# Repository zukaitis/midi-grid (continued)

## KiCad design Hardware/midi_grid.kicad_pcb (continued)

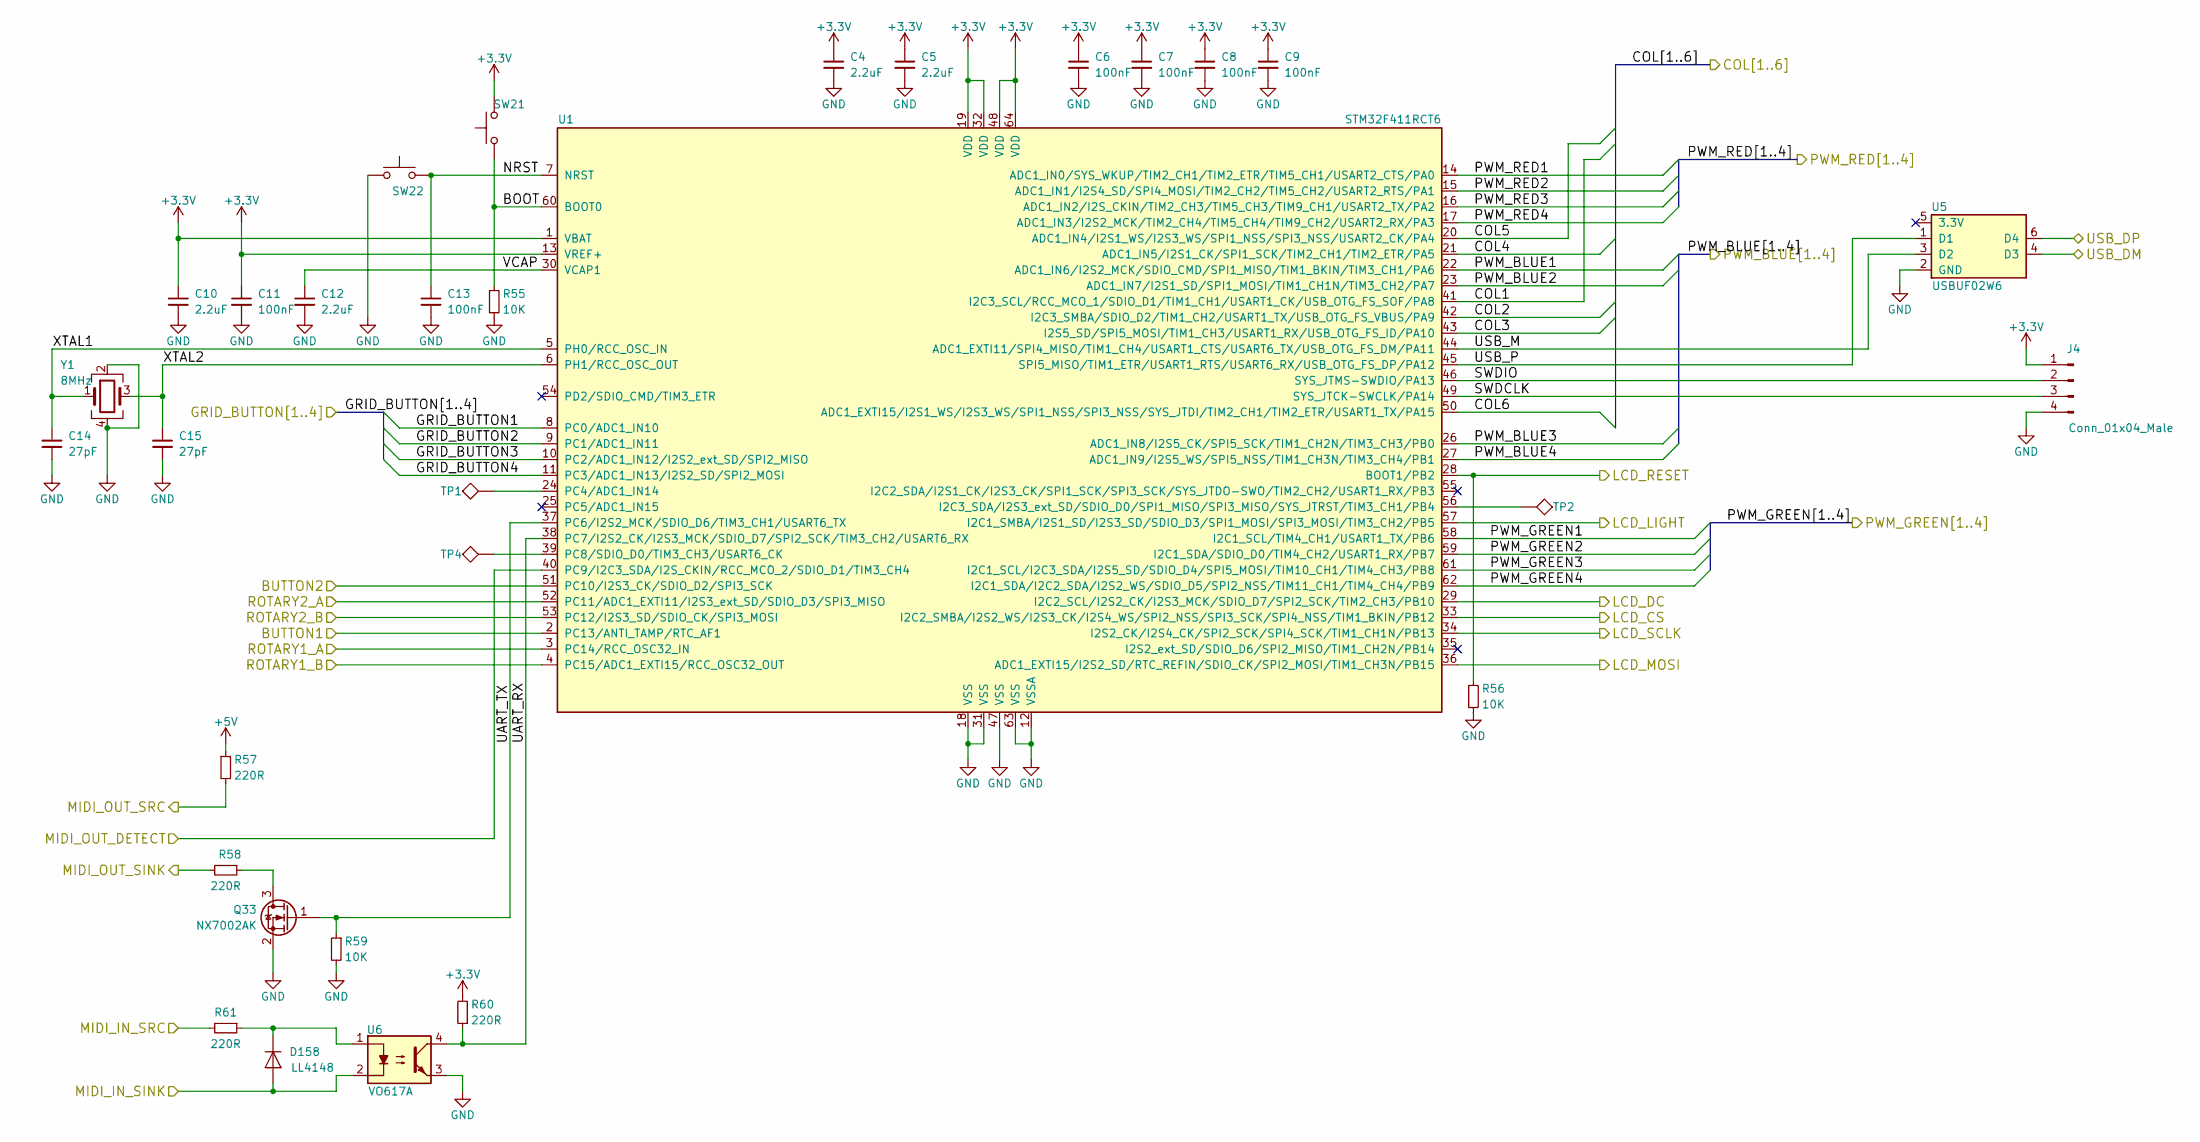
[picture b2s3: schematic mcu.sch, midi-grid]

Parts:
C4, C5, C10, C12: 2.2uF; C_0603
C6, C7, C8, C9, C11, C13: 100nF; C_0603
C14, C15: 27pF; C_0603
D158: LL4148; D_MiniMELF
J4: Conn_01x04_Male; Molex_KK-6410-04_04x2.54mm_Straight
Q33: NX7002AK; SOT-23
R55, R56, R59: 10K; R_0603
R57, R58, R60, R61: 220R; R_0603
SW21, SW22: SW_Push; SW_SPST_PTS645
TP1, TP2, TP4: TEST; Test_Point_Pad_d3.0mm
U1: STM32F411RCT6; LQFP-64_10x10mm_Pitch0.5mm
U5: USBUF02W6; SOT-363_SC-70-6
U6: VO617A; DIP4-smd
Y1: 8MHz; Oscillator_SMD_EuroQuartz_XO53-4pin_5.0x3.2mm_HandSoldering

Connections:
+3V3: C4.1, C5.1, C6.1, C7.1, C8.1, C9.1, C10.1, C11.1, J4.1, R60.2, SW21.2, U1.1 (VBAT), U1.13 (VREF+), U1.19 (VDD), U1.32 (VDD), U1.48 (VDD), U1.64 (VDD); also elsewhere on the board
+5V: R57.1; also elsewhere on the board
/digital_io/BUTTON1: U1.2 (PC13/ANTI_TAMP/RTC_AF1); also elsewhere on the board
/digital_io/BUTTON2: U1.51 (PC10/I2S3_CK/SDIO_D2/SPI3_SCK); also elsewhere on the board
/digital_io/LCD_CS: U1.33 (I2C2_SMBA/I2S2_WS/I2S3_CK/I2S4_WS/SPI2_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); also elsewhere on the board
/digital_io/LCD_DC: U1.29 (I2C2_SCL/I2S2_CK/I2S3_MCK/SDIO_D7/SPI2_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); also elsewhere on the board
/digital_io/LCD_LIGHT: U1.57 (I2C1_SMBA/I2S1_SD/I2S3_SD/SDIO_D3/SPI1_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); also elsewhere on the board
/digital_io/LCD_MOSI: U1.36 (ADC1_EXTI15/I2S2_SD/RTC_REFIN/SDIO_CK/S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); also elsewhere on the board
/digital_io/LCD_RESET: R56.1, U1.28 (BOOT1/PB2); also elsewhere on the board
/digital_io/LCD_SCLK: U1.34 (I2S2_CK/I2S4_CK/SPI2_SCK/SPI4_SCK/TIM1_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); also elsewhere on the board
/digital_io/ROTARY1_A: U1.3 (PC14/RCC_OSC32_IN); also elsewhere on the board
/digital_io/ROTARY1_B: U1.4 (PC15/ADC1_EXTI15/RCC_OSC32_OUT); also elsewhere on the board
/digital_io/ROTARY2_A: U1.52 (PC11/ADC1_EXTI11/I2S3_ext_SD/SDIO_D3/SP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); also elsewhere on the board
/digital_io/ROTARY2_B: U1.53 (PC12/I2S3_SD/SDIO_CK/SPI3_MOSI); also elsewhere on the board
/grid/GRID_BUTTON1: U1.8 (PC0/ADC1_IN10); also elsewhere on the board
/grid/GRID_BUTTON2: U1.9 (PC1/ADC1_IN11); also elsewhere on the board
/grid/GRID_BUTTON3: U1.10 (PC2/ADC1_IN12/I2S2_ext_SD/SPI2_MISO); also elsewhere on the board
/grid/GRID_BUTTON4: U1.11 (PC3/ADC1_IN13/I2S2_SD/SPI2_MOSI); also elsewhere on the board
/grid/PWM_BLUE1: U1.22 (ADC1_IN6/I2S2_MCK/SDIO_CMD/SPI1_MISO/TI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); also elsewhere on the board
/grid/PWM_BLUE2: U1.23 (ADC1_IN7/I2S1_SD/SPI1_MOSI/TIM1_CH1N/TI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); also elsewhere on the board
/grid/PWM_BLUE3: U1.26 (ADC1_IN8/I2S5_CK/SPI5_SCK/TIM1_CH2N/TIM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); also elsewhere on the board
/grid/PWM_BLUE4: U1.27 (ADC1_IN9/I2S5_WS/SPI5_NSS/TIM1_CH3N/TIM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); also elsewhere on the board
/grid/PWM_GREEN1: U1.58 (I2C1_SCL/TIM4_CH1/USART1_TX/PB6); also elsewhere on the board
/grid/PWM_GREEN2: U1.59 (I2C1_SDA/SDIO_D0/TIM4_CH2/USART1_RX/PB7); also elsewhere on the board
/grid/PWM_GREEN3: U1.61 (I2C1_SCL/I2C3_SDA/I2S5_SD/SDIO_D4/SPI5_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); also elsewhere on the board
/grid/PWM_GREEN4: U1.62 (I2C1_SDA/I2C2_SDA/I2S2_WS/SDIO_D5/SPI2_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); also elsewhere on the board
/grid/PWM_RED1: U1.14 (ADC1_IN0/SYS_WKUP/TIM2_CH1/TIM2_ETR/TIM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); also elsewhere on the board
/grid/PWM_RED2: U1.15 (ADC1_IN1/I2S4_SD/SPI4_MOSI/TIM2_CH2/TIM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); also elsewhere on the board
/grid/PWM_RED3: U1.16 (ADC1_IN2/I2S_CKIN/TIM2_CH3/TIM5_CH3/TIM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); also elsewhere on the board
/grid/PWM_RED4: U1.17 (ADC1_IN3/I2S2_MCK/TIM2_CH4/TIM5_CH4/TIM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); also elsewhere on the board
/mcu/BOOT: R55.1, SW21.1, U1.60 (BOOT0)
/mcu/COL1: U1.41 (I2C3_SCL/RCC_MCO_1/SDIO_D1/TIM1_CH1/USA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); also elsewhere on the board
/mcu/COL2: U1.42 (I2C3_SMBA/SDIO_D2/TIM1_CH2/USART1_TX/US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); also elsewhere on the board
/mcu/COL3: U1.43 (I2S5_SD/SPI5_MOSI/TIM1_CH3/USART1_RX/US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); also elsewhere on the board
/mcu/COL4: U1.21 (ADC1_IN5/I2S1_CK/SPI1_SCK/TIM2_CH1/TIM2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); also elsewhere on the board
/mcu/COL5: U1.20 (ADC1_IN4/I2S1_WS/I2S3_WS/SPI1_NSS/SPI3_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); also elsewhere on the board
/mcu/COL6: U1.50 (ADC1_EXTI15/I2S1_WS/I2S3_WS/SPI1_NSS/SP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); also elsewhere on the board
/mcu/MIDI_IN_SINK: D158.2 (A), U6.2; also elsewhere on the board
/mcu/MIDI_IN_SRC: R61.2; also elsewhere on the board
/mcu/MIDI_OUT_DETECT: U1.40 (PC9/I2C3_SDA/I2S_CKIN/RCC_MCO_2/SDIO_D1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); also elsewhere on the board
/mcu/MIDI_OUT_SINK: R58.2; also elsewhere on the board
/mcu/MIDI_OUT_SRC: R57.2; also elsewhere on the board
/mcu/NRST: C13.1, SW22.2, U1.7 (NRST)
/mcu/SWDCLK: J4.3, U1.49 (SYS_JTCK-SWCLK/PA14)
/mcu/SWDIO: J4.2, U1.46 (SYS_JTMS-SWDIO/PA13)
/mcu/UART_RX: R60.1, U1.38 (PC7/I2S2_CK/I2S3_MCK/SDIO_D7/SPI2_SCK/T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), U6.4
/mcu/UART_TX: Q33.1 (G), R59.1, U1.37 (PC6/I2S2_MCK/SDIO_D6/TIM3_CH1/USART6_TX)
/mcu/USB_DM: U5.4 (D3); also elsewhere on the board
/mcu/USB_DP: U5.6 (D4); also elsewhere on the board
/mcu/USB_M: U1.44 (ADC1_EXTI11/SPI4_MISO/TIM1_CH4/USART1_C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), U5.3 (D2)
/mcu/USB_P: U1.45 (SPI5_MISO/TIM1_ETR/USART1_RTS/USART6_RX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), U5.1 (D1)
/mcu/VCAP: C12.1, U1.30 (VCAP1)
/mcu/XTAL1: C14.1, U1.5 (PH0/RCC_OSC_IN), Y1.1
/mcu/XTAL2: C15.1, U1.6 (PH1/RCC_OSC_OUT), Y1.3
GND: C4.2, C5.2, C6.2, C7.2, C8.2, C9.2, C10.2, C11.2, C12.2, C13.2, C14.2, C15.2, J4.4, Q33.2 (S), R55.2, R56.2, R59.2, SW22.1, U1.12 (VSSA), U1.18 (VSS), U1.31 (VSS), U1.47 (VSS), U1.63 (VSS), U5.2 (GND), U6.3, Y1.2, Y1.4; also elsewhere on the board
unnamed: D158.1 (K), R61.1, U6.1
unnamed: Q33.3 (D), R58.1
unnamed: TP1.1, U1.24 (PC4/ADC1_IN14)
unnamed: TP2.1, U1.56 (I2C3_SDA/I2S3_ext_SD/SDIO_D0/SPI1_MISO/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)
unnamed: TP4.1, U1.39 (PC8/SDIO_D0/TIM3_CH3/USART6_CK)

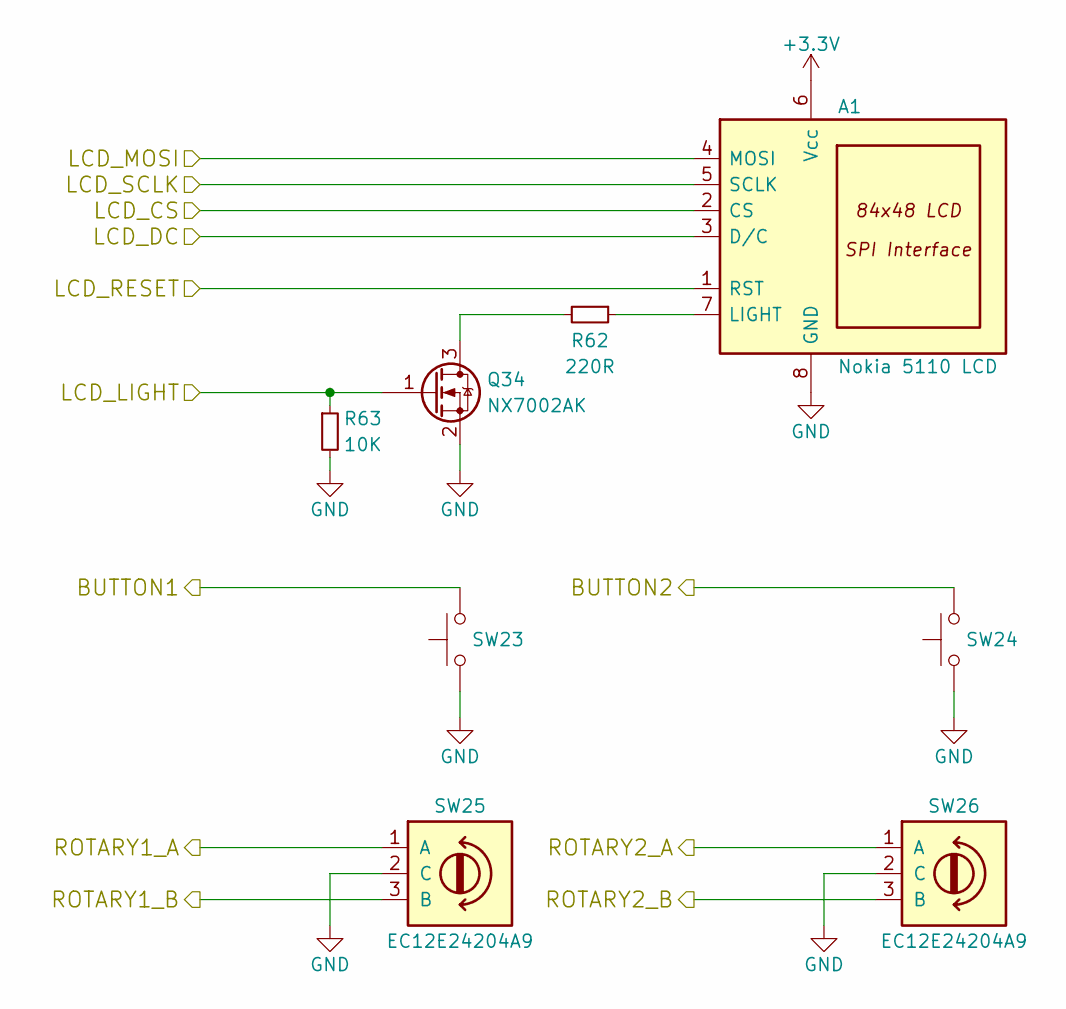
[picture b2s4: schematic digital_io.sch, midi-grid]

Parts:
A1: Nokia 5110 LCD; Nokia_5110_lcd
Q34: NX7002AK; SOT-23
R62: 220R; R_0603
R63: 10K; R_0603
SW23, SW24: SW_Push; Tactile_switch_12x12
SW25, SW26: EC12E24204A9; EC12

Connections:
+3V3: A1.6 (Vcc); also elsewhere on the board
/digital_io/BUTTON1: SW23.2; also elsewhere on the board
/digital_io/BUTTON2: SW24.2; also elsewhere on the board
/digital_io/LCD_CS: A1.2 (CS); also elsewhere on the board
/digital_io/LCD_DC: A1.3 (D/C); also elsewhere on the board
/digital_io/LCD_LIGHT: Q34.1 (G), R63.1; also elsewhere on the board
/digital_io/LCD_MOSI: A1.4 (MOSI); also elsewhere on the board
/digital_io/LCD_RESET: A1.1 (RST); also elsewhere on the board
/digital_io/LCD_SCLK: A1.5 (SCLK); also elsewhere on the board
/digital_io/ROTARY1_A: SW25.1 (A); also elsewhere on the board
/digital_io/ROTARY1_B: SW25.3 (B); also elsewhere on the board
/digital_io/ROTARY2_A: SW26.1 (A); also elsewhere on the board
/digital_io/ROTARY2_B: SW26.3 (B); also elsewhere on the board
GND: A1.8 (GND), Q34.2 (S), R63.2, SW23.1, SW24.1, SW25.2 (C), SW26.2 (C); also elsewhere on the board
unnamed: A1.7 (LIGHT), R62.1
unnamed: Q34.3 (D), R62.2

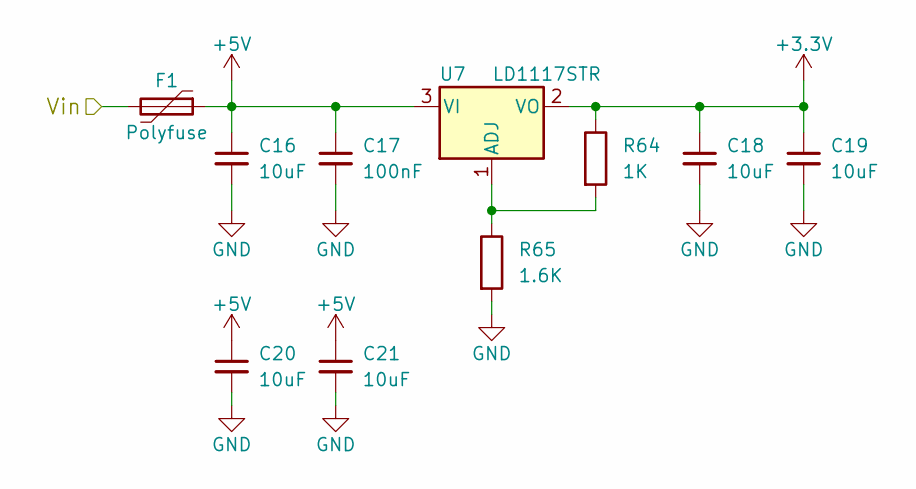
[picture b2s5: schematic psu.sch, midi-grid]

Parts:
C16, C18, C19, C20, C21: 10uF; C_1206
C17: 100nF; C_0603
F1: Polyfuse; R_1206
R64: 1K; R_0603
R65: 1.6K; R_0603
U7: LD1117STR; SOT-223-3Lead_TabPin2

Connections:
+3V3: C18.1, C19.1, R64.1, U7.2 (VO); also elsewhere on the board
+5V: C16.1, C17.1, C20.1, C21.1, F1.1, U7.3 (VI); also elsewhere on the board
/psu/Vin: F1.2; also elsewhere on the board
GND: C16.2, C17.2, C18.2, C19.2, C20.2, C21.2, R65.2; also elsewhere on the board
unnamed: R64.2, R65.1, U7.1 (ADJ)

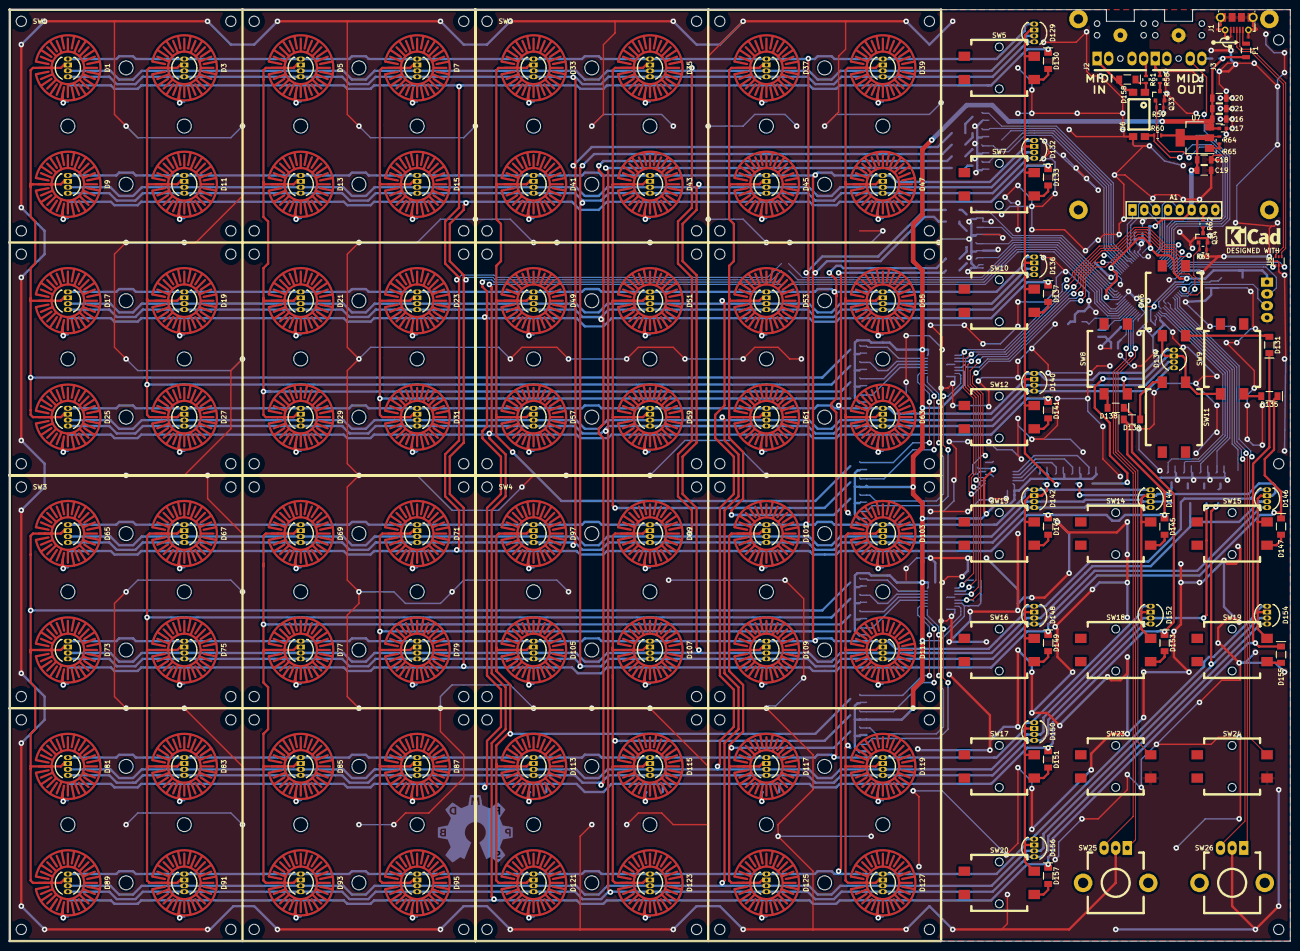
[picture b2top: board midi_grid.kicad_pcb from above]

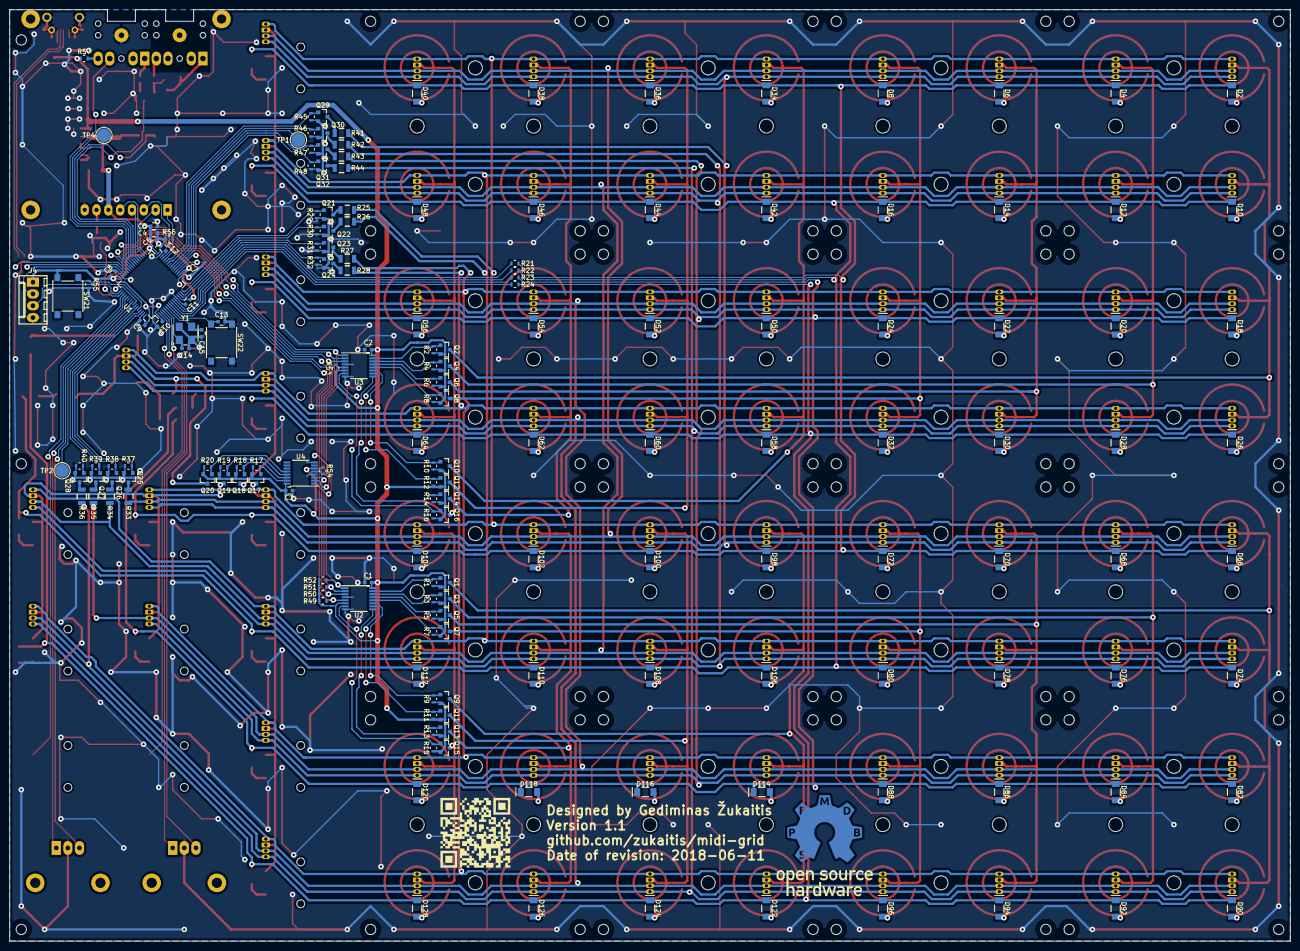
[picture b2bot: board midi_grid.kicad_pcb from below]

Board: 2 copper layers, 275.0 x 200.0 mm, 328 parts (181 on the bottom side), 212 nets.

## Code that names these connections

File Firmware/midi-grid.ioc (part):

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Mcu.Name=STM32F411R(C-E)Tx
Mcu.Package=LQFP64
Mcu.UserName=STM32F411RCTx
PA0-WKUP.GPIOParameters=GPIO_ModeDefaultPP,GPIO_Speed,GPIO_PuPd,GPIO_Label
PA0-WKUP.GPIO_Label=PWM_RED1
PA0-WKUP.GPIO_ModeDefaultPP=GPIO_MODE_AF_PP
PA0-WKUP.GPIO_PuPd=GPIO_PULLDOWN
PA0-WKUP.GPIO_Speed=GPIO_SPEED_FREQ_VERY_HIGH
PA0-WKUP.Signal=S_TIM2_CH1_ETR
PA1.GPIOParameters=GPIO_ModeDefaultPP,GPIO_Speed,GPIO_PuPd,GPIO_Label
PA1.GPIO_Label=PWM_RED2
PA1.GPIO_ModeDefaultPP=GPIO_MODE_AF_PP
PA1.GPIO_PuPd=GPIO_PULLDOWN
PA1.GPIO_Speed=GPIO_SPEED_FREQ_VERY_HIGH
PA1.Signal=S_TIM2_CH2
PA10.GPIOParameters=GPIO_Speed,PinState,GPIO_Label,GPIO_ModeDefaultOutputPP
PA10.GPIO_Label=GRID_COLUMN_OUT3
PA10.GPIO_ModeDefaultOutputPP=GPIO_MODE_OUTPUT_OD
PA10.GPIO_Speed=GPIO_SPEED_FREQ_VERY_HIGH
PA10.PinState=GPIO_PIN_SET
PA10.Signal=GPIO_Output
PA11.GPIOParameters=GPIO_Label
PA11.GPIO_Label=USB_DM
PA11.Mode=Device_Only
PA11.Signal=USB_OTG_FS_DM
PA12.GPIOParameters=GPIO_Label
PA12.GPIO_Label=USB_DP
PA12.Mode=Device_Only
PA12.Signal=USB_OTG_FS_DP
PA13.GPIOParameters=GPIO_Label
PA13.GPIO_Label=SWDIO
PA13.Mode=Serial_Wire
PA13.Signal=SYS_JTMS-SWDIO
PA14.GPIOParameters=GPIO_Label
PA14.GPIO_Label=SWDCLK
PA14.Mode=Serial_Wire
PA14.Signal=SYS_JTCK-SWCLK
PA15.GPIOParameters=GPIO_Speed,PinState,GPIO_Label,GPIO_ModeDefaultOutputPP
PA15.GPIO_Label=GRID_COLUMN_OUT6
PA15.GPIO_ModeDefaultOutputPP=GPIO_MODE_OUTPUT_OD
PA15.GPIO_Speed=GPIO_SPEED_FREQ_VERY_HIGH
PA15.PinState=GPIO_PIN_SET
PA15.Signal=GPIO_Output
PA2.GPIOParameters=GPIO_ModeDefaultPP,GPIO_Speed,GPIO_PuPd,GPIO_Label
PA2.GPIO_Label=PWM_RED3
PA2.GPIO_ModeDefaultPP=GPIO_MODE_AF_PP
PA2.GPIO_PuPd=GPIO_PULLDOWN
PA2.GPIO_Speed=GPIO_SPEED_FREQ_VERY_HIGH
PA2.Signal=S_TIM2_CH3
PA3.GPIOParameters=GPIO_ModeDefaultPP,GPIO_Speed,GPIO_PuPd,GPIO_Label
PA3.GPIO_Label=PWM_RED4
PA3.GPIO_ModeDefaultPP=GPIO_MODE_AF_PP
PA3.GPIO_PuPd=GPIO_PULLDOWN
PA3.GPIO_Speed=GPIO_SPEED_FREQ_VERY_HIGH
PA3.Signal=S_TIM2_CH4
PA4.GPIOParameters=GPIO_Speed,PinState,GPIO_Label,GPIO_ModeDefaultOutputPP
PA4.GPIO_Label=GRID_COLUMN_OUT5
PA4.GPIO_ModeDefaultOutputPP=GPIO_MODE_OUTPUT_OD
PA4.GPIO_Speed=GPIO_SPEED_FREQ_VERY_HIGH
PA4.PinState=GPIO_PIN_SET
PA4.Signal=GPIO_Output
PA5.GPIOParameters=GPIO_Speed,PinState,GPIO_Label,GPIO_ModeDefaultOutputPP
PA5.GPIO_Label=GRID_COLUMN_OUT4
PA5.GPIO_ModeDefaultOutputPP=GPIO_MODE_OUTPUT_OD
PA5.GPIO_Speed=GPIO_SPEED_FREQ_VERY_HIGH
PA5.PinState=GPIO_PIN_SET
PA5.Signal=GPIO_Output
PA6.GPIOParameters=GPIO_ModeDefaultPP,GPIO_Speed,GPIO_PuPd,GPIO_Label
PA6.GPIO_Label=PWM_BLUE1
PA6.GPIO_ModeDefaultPP=GPIO_MODE_AF_PP
PA6.GPIO_PuPd=GPIO_PULLDOWN
PA6.GPIO_Speed=GPIO_SPEED_FREQ_VERY_HIGH
PA6.Signal=S_TIM3_CH1
PA7.GPIOParameters=GPIO_ModeDefaultPP,GPIO_Speed,GPIO_PuPd,GPIO_Label
PA7.GPIO_Label=PWM_BLUE2
PA7.GPIO_ModeDefaultPP=GPIO_MODE_AF_PP
PA7.GPIO_PuPd=GPIO_PULLDOWN
PA7.GPIO_Speed=GPIO_SPEED_FREQ_VERY_HIGH
PA7.Signal=S_TIM3_CH2
PA8.GPIOParameters=GPIO_Speed,PinState,GPIO_Label,GPIO_ModeDefaultOutputPP
PA8.GPIO_Label=GRID_COLUMN_OUT1
PA8.GPIO_ModeDefaultOutputPP=GPIO_MODE_OUTPUT_OD
PA8.GPIO_Speed=GPIO_SPEED_FREQ_VERY_HIGH
PA8.PinState=GPIO_PIN_SET
PA8.Signal=GPIO_Output
PA9.GPIOParameters=GPIO_Speed,PinState,GPIO_Label,GPIO_ModeDefaultOutputPP
PA9.GPIO_Label=GRID_COLUMN_OUT2
PA9.GPIO_ModeDefaultOutputPP=GPIO_MODE_OUTPUT_OD
PA9.GPIO_Speed=GPIO_SPEED_FREQ_VERY_HIGH
PA9.PinState=GPIO_PIN_SET
PA9.Signal=GPIO_Output
PB0.GPIOParameters=GPIO_ModeDefaultPP,GPIO_Speed,GPIO_PuPd,GPIO_Label
PB0.GPIO_Label=PWM_BLUE3
PB0.GPIO_ModeDefaultPP=GPIO_MODE_AF_PP
PB0.GPIO_PuPd=GPIO_PULLDOWN
PB0.GPIO_Speed=GPIO_SPEED_FREQ_VERY_HIGH
PB0.Signal=S_TIM3_CH3
PB1.GPIOParameters=GPIO_ModeDefaultPP,GPIO_Speed,GPIO_PuPd,GPIO_Label
PB1.GPIO_Label=PWM_BLUE4
PB1.GPIO_ModeDefaultPP=GPIO_MODE_AF_PP
PB1.GPIO_PuPd=GPIO_PULLDOWN
PB1.GPIO_Speed=GPIO_SPEED_FREQ_VERY_HIGH
PB1.Signal=S_TIM3_CH4
PB10.GPIOParameters=GPIO_Speed,PinState,GPIO_PuPd,GPIO_Label
PB10.GPIO_Label=LCD_DC
PB10.GPIO_PuPd=GPIO_PULLUP
PB10.GPIO_Speed=GPIO_SPEED_FREQ_HIGH
PB10.PinState=GPIO_PIN_SET
PB10.Signal=GPIO_Output
PB12.GPIOParameters=GPIO_Label
PB12.GPIO_Label=LCD_CS
PB12.Mode=NSS_Signal_Hard_Output
PB12.Signal=SPI2_NSS
PB13.GPIOParameters=GPIO_Label
PB13.GPIO_Label=LCD_SCK
PB13.Mode=TX_Only_Simplex_Unidirect_Master
PB13.Signal=SPI2_SCK
PB14.GPIOParameters=GPIO_Label
PB14.GPIO_Label=LCD_LIGHT
PB14.Mode=PWM Generation2 CH2N
PB14.Signal=TIM1_CH2N
PB15.GPIOParameters=GPIO_Label
PB15.GPIO_Label=LCD_MOSI
PB15.Mode=TX_Only_Simplex_Unidirect_Master
PB15.Signal=SPI2_MOSI
PB2.GPIOParameters=GPIO_Speed,PinState,GPIO_PuPd,GPIO_Label
PB2.GPIO_Label=LCD_RESET
PB2.GPIO_PuPd=GPIO_PULLUP
PB2.GPIO_Speed=GPIO_SPEED_FREQ_HIGH
PB2.PinState=GPIO_PIN_SET
PB2.Signal=GPIO_Output
PB6.GPIOParameters=GPIO_ModeDefaultPP,GPIO_Speed,GPIO_PuPd,GPIO_Label
PB6.GPIO_Label=PWM_GREEN1
PB6.GPIO_ModeDefaultPP=GPIO_MODE_AF_PP
PB6.GPIO_PuPd=GPIO_PULLDOWN
PB6.GPIO_Speed=GPIO_SPEED_FREQ_VERY_HIGH
PB6.Signal=S_TIM4_CH1
PB7.GPIOParameters=GPIO_ModeDefaultPP,GPIO_Speed,GPIO_PuPd,GPIO_Label
PB7.GPIO_Label=PWM_GREEN2
PB7.GPIO_ModeDefaultPP=GPIO_MODE_AF_PP
PB7.GPIO_PuPd=GPIO_PULLDOWN
PB7.GPIO_Speed=GPIO_SPEED_FREQ_VERY_HIGH
PB7.Signal=S_TIM4_CH2
PB8.GPIOParameters=GPIO_ModeDefaultPP,GPIO_Speed,GPIO_PuPd,GPIO_Label
PB8.GPIO_Label=PWM_GREEN3
PB8.GPIO_ModeDefaultPP=GPIO_MODE_AF_PP
PB8.GPIO_PuPd=GPIO_PULLDOWN
PB8.GPIO_Speed=GPIO_SPEED_FREQ_VERY_HIGH
PB8.Signal=S_TIM4_CH3
PB9.GPIOParameters=GPIO_ModeDefaultPP,GPIO_Speed,GPIO_PuPd,GPIO_Label
PB9.GPIO_Label=PWM_GREEN4
PB9.GPIO_ModeDefaultPP=GPIO_MODE_AF_PP
PB9.GPIO_PuPd=GPIO_PULLDOWN
PB9.GPIO_Speed=GPIO_SPEED_FREQ_VERY_HIGH
PB9.Signal=S_TIM4_CH4
PC0.GPIOParameters=GPIO_PuPd,GPIO_Label,GPIO_Mode
PC0.GPIO_Label=GRID_BUTTON_IN1
PC0.GPIO_Mode=GPIO_MODE_INPUT
PC0.GPIO_PuPd=GPIO_PULLDOWN
PC0.Signal=GPIO_Input
PC1.GPIOParameters=GPIO_PuPd,GPIO_Label,GPIO_Mode
PC1.GPIO_Label=GRID_BUTTON_IN2
PC1.GPIO_Mode=GPIO_MODE_INPUT
PC1.GPIO_PuPd=GPIO_PULLDOWN
PC1.Signal=GPIO_Input
PC10.GPIOParameters=GPIO_PuPd,GPIO_Label,GPIO_Mode
PC10.GPIO_Label=BUTTON_IN2
PC10.GPIO_Mode=GPIO_MODE_INPUT
PC10.GPIO_PuPd=GPIO_PULLUP
PC10.Signal=GPIO_Input
PC11.GPIOParameters=GPIO_PuPd,GPIO_Label,GPIO_Mode
PC11.GPIO_Label=ROTARY2_A
PC11.GPIO_Mode=GPIO_MODE_INPUT
PC11.GPIO_PuPd=GPIO_PULLUP
PC11.Signal=GPIO_Input
PC12.GPIOParameters=GPIO_PuPd,GPIO_Label,GPIO_Mode
PC12.GPIO_Label=ROTARY2_B
PC12.GPIO_Mode=GPIO_MODE_INPUT
PC12.GPIO_PuPd=GPIO_PULLUP
PC12.Signal=GPIO_Input
PC13-ANTI_TAMP.GPIOParameters=GPIO_PuPd,GPIO_Label,GPIO_Mode
PC13-ANTI_TAMP.GPIO_Label=BUTTON_IN1
PC13-ANTI_TAMP.GPIO_Mode=GPIO_MODE_INPUT
PC13-ANTI_TAMP.GPIO_PuPd=GPIO_PULLUP
PC13-ANTI_TAMP.Signal=GPIO_Input
PC14-OSC32_IN.GPIOParameters=GPIO_PuPd,GPIO_Label,GPIO_Mode
PC14-OSC32_IN.GPIO_Label=ROTARY1_A
PC14-OSC32_IN.GPIO_Mode=GPIO_MODE_INPUT
PC14-OSC32_IN.GPIO_PuPd=GPIO_PULLUP
PC14-OSC32_IN.Signal=GPIO_Input
PC15-OSC32_OUT.GPIOParameters=GPIO_PuPd,GPIO_Label,GPIO_Mode
PC15-OSC32_OUT.GPIO_Label=ROTARY1_B
PC15-OSC32_OUT.GPIO_Mode=GPIO_MODE_INPUT
PC15-OSC32_OUT.GPIO_PuPd=GPIO_PULLUP
PC15-OSC32_OUT.Signal=GPIO_Input
PC2.GPIOParameters=GPIO_PuPd,GPIO_Label,GPIO_Mode
PC2.GPIO_Label=GRID_BUTTON_IN3
PC2.GPIO_Mode=GPIO_MODE_INPUT
PC2.GPIO_PuPd=GPIO_PULLDOWN
PC2.Signal=GPIO_Input
PC3.GPIOParameters=GPIO_PuPd,GPIO_Label,GPIO_Mode
PC3.GPIO_Label=GRID_BUTTON_IN4
PC3.GPIO_Mode=GPIO_MODE_INPUT
PC3.GPIO_PuPd=GPIO_PULLDOWN
PC3.Signal=GPIO_Input
PC4.Signal=ADCx_IN14
PC6.GPIOParameters=GPIO_Label
PC6.GPIO_Label=MIDI_OUT
PC6.Mode=Asynchronous
PC6.Signal=USART6_TX
PC7.GPIOParameters=GPIO_Label
PC7.GPIO_Label=MIDI_IN
PC7.Mode=Asynchronous
PC7.Signal=USART6_RX
PC9.GPIOParameters=GPIO_PuPd,GPIO_Label
PC9.GPIO_Label=MIDI_OUT_DETECT
PC9.GPIO_PuPd=GPIO_PULLDOWN
PC9.Signal=GPIO_Input
PH0\ -\ OSC_IN.Mode=HSE-External-Oscillator
PH0\ -\ OSC_IN.Signal=RCC_OSC_IN
PH1\ -\ OSC_OUT.Mode=HSE-External-Oscillator
PH1\ -\ OSC_OUT.Signal=RCC_OSC_OUT
RCC.HSE_VALUE=8000000
RCC.SYSCLKFreq_VALUE=96000000
RCC.SYSCLKSource=RCC_SYSCLKSOURCE_PLLCLK
board=midi-grid

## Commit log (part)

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2018-01-04 removed .bak files
2018-01-04 multiple schematic and pcb changes
2018-01-05 pcb in development
2018-01-07 commiting before bulk led schematic symbol change
2018-01-07 successfuly changed component symbols and net names, further developed pcb
2018-01-09 added net names in grid schematic
2018-01-10 initializing new repo
2018-01-20 deleting all the files from repo for a fresh start
2018-01-20 adding hardware files
2018-01-20 added early readme of whole project
2018-01-24 added BOM, changed names of some components in the schematic
2018-01-24 added image of PCB 3D render
2018-01-25 copied project cache library to project_library.lib
2018-01-25 added CubeMX project, re-generated a PDF schematic
2018-01-27 changed pin of LCD CS, so hardware chip select could be used
2018-01-28 added c project files
2018-01-28 removed .gitignore file from the repo
2018-01-28 added readme for hardware folder
2018-01-28 edited hardware readme
2018-01-31 managed to run program on device, added debugger configuration file
2018-02-01 wrote PWM timer initialization function
2018-02-03 managed to light some leds
2018-02-04 adopted almost all functions from the prototype, leds can be set using midi messages
2018-02-07 leds and buttons are working
2018-02-08 added random light animation and usb connection checking functions, removed some unused code from msp and main files
2018-02-09 added brightness measurement function, it does not work yet
2018-02-12 configured semihosting
2018-02-13 started implementing different layouts
2018-02-18 added lcd files, lcd isn
2018-02-19 added function to transmit SysEx messages, haven't tested it yet
2018-02-23 fixed SysEx message transmission, Launchpad95 loads now
2018-02-25 managed to control lcd using SPI and DMA
2018-02-26 fixed pulsing led issue, added some lcd functionality
2018-02-28 added video link
2018-02-28 implemented Launchpad95 mode acquisition
2018-03-04 renamed user files with c++ extensions, project compiles and works again
2018-03-04 managed to rework lcd functions into c++ classes
2018-03-07 continuing transition to c++, code does not compile now
2018-03-08 moving grid further to c++
2018-03-10 escaped circular dependency hell, project builds and works
2018-03-11 rewriten usb midi interface into c++, everything works
2018-03-11 managed to enable lcd backlight pwm
2018-03-12 added missing images file
2018-03-12 added gitattributes file
2018-03-13 added midi activity functionality, although it has some nasty bug
2018-03-14 changed status bar, increased optimization level
2018-03-18 added license for real
2018-03-19 improved gui by adding more logic to it
2018-03-20 changed VID/PID, expanded readme
2018-04-01 implemented timing status functionality, fixed a ring buffer issue by momentarily disabling interrupts
2018-04-02 adjusted gui items' shapes and positions
2018-04-14 implemented readout of rotary endoders
2018-04-14 implemented progress arc display
2018-04-25 added 3D model of the case
2018-05-01 implemented smooth backlight intensity transition
2018-05-09 added reset to bootloader functionality, device can now be updated through USB using ST's Dfuse tool
2018-05-13 newly generated status icons
2018-05-20 cleaned up main, moved unused functions, removed msp file
2018-05-29 set optimization to -O0, works for now
2018-05-30 refactored Grid and GridControl classes
2018-06-06 made cosmetic changes for most of the classes, reverted LcdControl class files to working revision
2018-06-06 fixed some style issues in LcdControl class
2018-06-08 added bunch of const qualifiers for variables and parameters
2018-06-09 implemented backlight intensity control using SPI
2018-06-10 moved lcd backlight's stuff to separate class, fixed compiler warnings in HAL
2018-06-10 fixed a link in readme
2018-06-11 rerouted LCD_LIGHT pin to PB5
2018-06-26 introduced changes suggested by Cppcheck, updated Hardware readme
2018-07-01 expanded/edited readme files
2018-07-10 everything seems to work, no idea why, though
2018-07-13 refactored GridControl class, introduced name changes to others
2018-08-14 expanded hardware README
2018-08-15 added some color to images
2018-09-13 replaced names 'row' and 'column' into more distinguishable ones for grid control, changed configuration to run on Linux
2018-09-25 changed some constant names, moved and refactored getRandomColour() method
2018-10-02 made all HAL *InitTypeDef structures static, which fixed all strange issues for now. Improved architecture
2018-10-04 removed hal from almost all class header files, added global interrupts class
2018-10-07 removed unnecessary namespaces, made changes to hide implementation details
2018-10-07 started refactoring Launchpad class
2018-10-09 changed class and namespace names once again, added grid boot animation
2018-10-09 replaced 'colour' with 'color' globally
2018-10-11 fixed Images readme
2018-10-11 put images into table
2018-10-13 refactored magic numbers in Launchpad class
2018-10-16 refactored magic numbers in Launchpad class, fixed operation before midi is received
2018-11-02 removed some magic numbers from Launchpad class
2018-11-04 added midi icon to gui, changed video link
2019-03-16 replaced refresh led calls with FreeRTOS timer classes
2019-03-21 replaces FreeRTOStimers with threads, made Lcd class into a thread
2019-03-25 added mechanical parts to BOM
2019-03-28 got rid of HAL tick calls, and whole Time class
2019-04-03 enforced usage of freertos queue in Grid class
2019-04-08 replaced queue32 implementation with freertos queue, fixed additional button delay bug
2019-04-16 replaced multiple arguments with one in grid class
2019-05-02 moving to different branch before testing
2019-05-02 added new files
2019-05-02 the struggle continues
2019-05-13 everything compiles, does not run tho
2019-06-04 found a nasty mistake, now at least something works
2019-06-09 removed some redundant code, fixed a few issues
2019-06-13 fixed rand issue
2019-06-18 implemented the snake game
2019-06-19 made some improvements to Snake
2019-06-27 removed GUI class, moved all gui stuff into application classes, split launchpad class into main and gui one
2019-06-30 moved files and namespaces, fixed most of the known issues
2019-11-07 refactored Color class
2019-11-08 moved type implementation to types dir, updated Color unit tests
2019-11-11 ButtonAction naming and usage improvement
2019-11-21 refactored AdditionalButtons
2019-11-21 converted ButtonAction into enum class
2019-11-23 added etl as a submodule
2019-11-23 removed copied FreeRTOS files, added it as a submodule
2019-11-23 moved freertos-addons into submodule
2019-11-23 added freertos name into include path
2019-11-23 replaced freertos include quotation marks with angle brackets
2019-11-27 added early cmake generator file
2019-12-01 Friendship ended with make and cmake. Now ninja is my best friend
2019-12-05 removed all sw4stm32 files, gonna try to work exclussively in vscode now
2019-12-05 fixed pulsing LED bug
2019-12-15 added ninja build generator for individual unit test running
2019-12-17 wrote a script to run UTs, made some other nice changes
2019-12-18 modified run unit tests script to show statistics of tests ran
2019-12-19 implemented GridLedOutput unit test
2019-12-20 implemented GridFlashingLedsTest
2019-12-21 implemented a unit test for Grid class
2019-12-22 implemented unit test coverage report generation
2019-12-24 removed infinite loops from Thread::Run() methods, added mechanism to call private thread methods in unit tests
2019-12-24 added queue mock and unfinished grid button input test
2019-12-28 lcd refactoring is in progress, changes on every turn
2019-12-31 added backlight interface, moved it to separate folder, renamed color getters
2020-01-01 moved lcd output buffer specifics to driver file, made changes to lcd file structure
2020-01-08 fixed unit test coverage issue, by separating file under test from other src files
2020-01-08 employed clang to build UTs, added color and fixed links in unit test output
2020-01-10 set up llvm to compile the firmware, fixed places, which some of errors and warnings, spotted by clang
2020-01-11 upgraded/downgraded submodules to latest revisions
2020-01-11 added llvm setup step to build workflow and fixed intendation in ut workflow
2020-01-11 set workflows to run, when changes are made to their configs
2020-01-11 fixed few CI issues
2020-01-12 updated GNU ARM tools to newest version, fixed linker warnings
2020-01-12 added more unit tests, fixed recently spotted issues
2020-01-14 yet another atempt to fix the builds
2020-01-14 yet another atempt to fix the CI
2020-01-16 implemented semantic versioning system
2020-01-16 fixed an issue in get_version script
2020-01-16 atempting to adapt get_version script for CI
2020-01-17 updated checkout action version, maybe this will have some effect
2020-01-17 added info about submodules to README
2020-01-17 continuing to investigate secrets of github workflow
2020-01-17 looks like pre-releasing is not gonna work for now
2020-01-18 got rid of io directory
2020-01-23 restored MIDI input functionality by hacky means
2020-01-28 fixed unknown_typename error
2020-01-28 fixed readability-avoid-const-params-in-decls warnings
2020-01-28 fixed google-readability-namespace-comments warnings
2020-01-28 fixed google-readability-todo warnings
2020-01-28 fixed google-explicit-constructor warnings
2020-02-01 replaced some non-const references with pointers, hopefully fixed one of the craziness inducing bugs
2020-02-02 recovered UTs, making all kinds of changes, since nothing works anyway
2020-02-07 replaced some c-style arrays with etl ones
2020-02-07 added gerber files for hardware version v1.1
2020-02-16 everything except communication with Ableton works now
2020-02-19 updated FreeRTOS kernel, hopefully this will fix CI build
2020-02-22 implemented an acceptable firmware update workflow
2020-02-23 Fixed failing UT
2020-02-26 wrote first test steps
2020-03-30 implemented a primitive log, fixed a bug in lcd clearArea method
2020-03-31 added new SysEx functionality, and a test that covers it
2020-04-01 added sysex transmission test
2020-04-03 added disconnect command, implemented compdb generation
2020-04-04 updated gitignore
2020-04-05 implemented LCD priority manager
2020-04-06 added skeleton of log storage class
2020-04-07 changed parameter type of print methods
2020-04-08 fixed log storage, and added an UT for it
2020-04-11 added files, no signs of life from LCD yet
2020-04-11 LCD works now, fixed UT
2020-04-12 got LCD to work
2020-04-13 added minimal support for colors
2020-04-17 added base for Font class and font converter
2020-04-19 got new font to work, feels good
2020-04-19 replaced resistor and capacitor models
2020-04-20 converted all components except big tactile switches
2020-04-21 replaced all models with .step, deleted .wrl models
2020-04-23 managed to display a massive USB logo
2020-04-24 implemented interlacing in screen clearing, it somehow works
2020-04-25 fixed setArea issue by increasing optimization
2020-04-26 implemented alternate fill method, which utilizes interlacing
2020-04-26 implemented alternate putImage method, which utilizes interlacing
2020-04-27 refactored putString method
2020-04-28 added new big fonts
2020-05-06 implemented bpm display, finally
2020-05-12 added Draw class, lines work fine already
2020-05-19 finally implemented a somehow working arc drawing algorithm
2020-05-23 refactored color class to use values up to 255
2020-05-24 implemented primitive mode display
2020-05-25 made some nice changes to launchpad and its gui
2020-06-04 renamed Image class to ImageMono, replaced microcontroller with STM32F413RH
2020-07-14 fixed colors
2020-07-20 added Vector type, implemented a nice knob view
2020-08-15 implemented clip and track views with colors matching ones in Ableton
2020-08-15 added a step to setup clang for unit tests
2020-08-15 added a signature acquisition step for clang setup
2020-08-15 and another one
2020-08-15 why not one more
2020-09-17 commiting before branch switch
2020-09-20 added files of LCD module PCB
2021-04-22 dummy commit to rerun CI
2022-02-09 something's being built
2022-02-09 added files from src directory
2022-03-02 IT WORKSgit statusexit
